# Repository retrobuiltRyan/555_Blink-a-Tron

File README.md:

# 555_Blink-a-Tron
Surface Mount device practice soldering activity.
Blink LEDS without logic using 555 timer + TLC5916 LED driver: 

Source reference TI white paper: https://www.ti.com/lit/an/slva346/slva346.pdf?ts=1731359344476&ref_url=https%253A%252F%252Fwww.google.com%252F

## Bill of Materials (BOM)

| Reference     | Value       | Footprint                                             | Qty | DigiKey P/N          |
|---------------|-------------|--------------------------------------------------------|-----|-----------------------|
| BT1           | Battery     | Battery:BatteryHolder_Keystone_1058_1x2032            | 1   | BU2032SM-GCT-ND       |
| C1, C2, C3    | 0.1uF       | Capacitor_SMD:C_1206_3216Metric                        | 3   | 1292-1605-1-ND        |
| C4            | 1uF         | Capacitor_SMD:C_1206_3216Metric                        | 1   | 1276-1068-1-ND        |
| D1–D8         | D           | Diode_SMD:D_1206_3216Metric                            | 8   | 67-1359-1-ND          |
| R1            | 37.4k       | Resistor_SMD:R_1206_3216Metric                         | 1   | 311-37.4KFRCT-ND      |
| R2            | 20k         | Resistor_SMD:R_1206_3216Metric                         | 1   | 311-20.0KFRCT-ND      |
| R3            | 3k – 6k     | Resistor_SMD:R_1206_3216Metric                         | 1   | 311-6.2KERCT-ND       |
| SW1           | SW_Push     | Button_Switch_SMD:SW_SPST_Omron_B3FS-100xP            | 1   | CKN12221-1-ND         |
| U1            | ICM7555xB   | Package_SO:SOIC-8_3.9x4.9mm_P1.27mm                    | 1   | 296-1336-1-ND         |
| U2            | TLC5916     | Package_SO:SOIC-16_3.9x9.9mm_P1.27mm                   | 1   | 296-22710-1-ND        |

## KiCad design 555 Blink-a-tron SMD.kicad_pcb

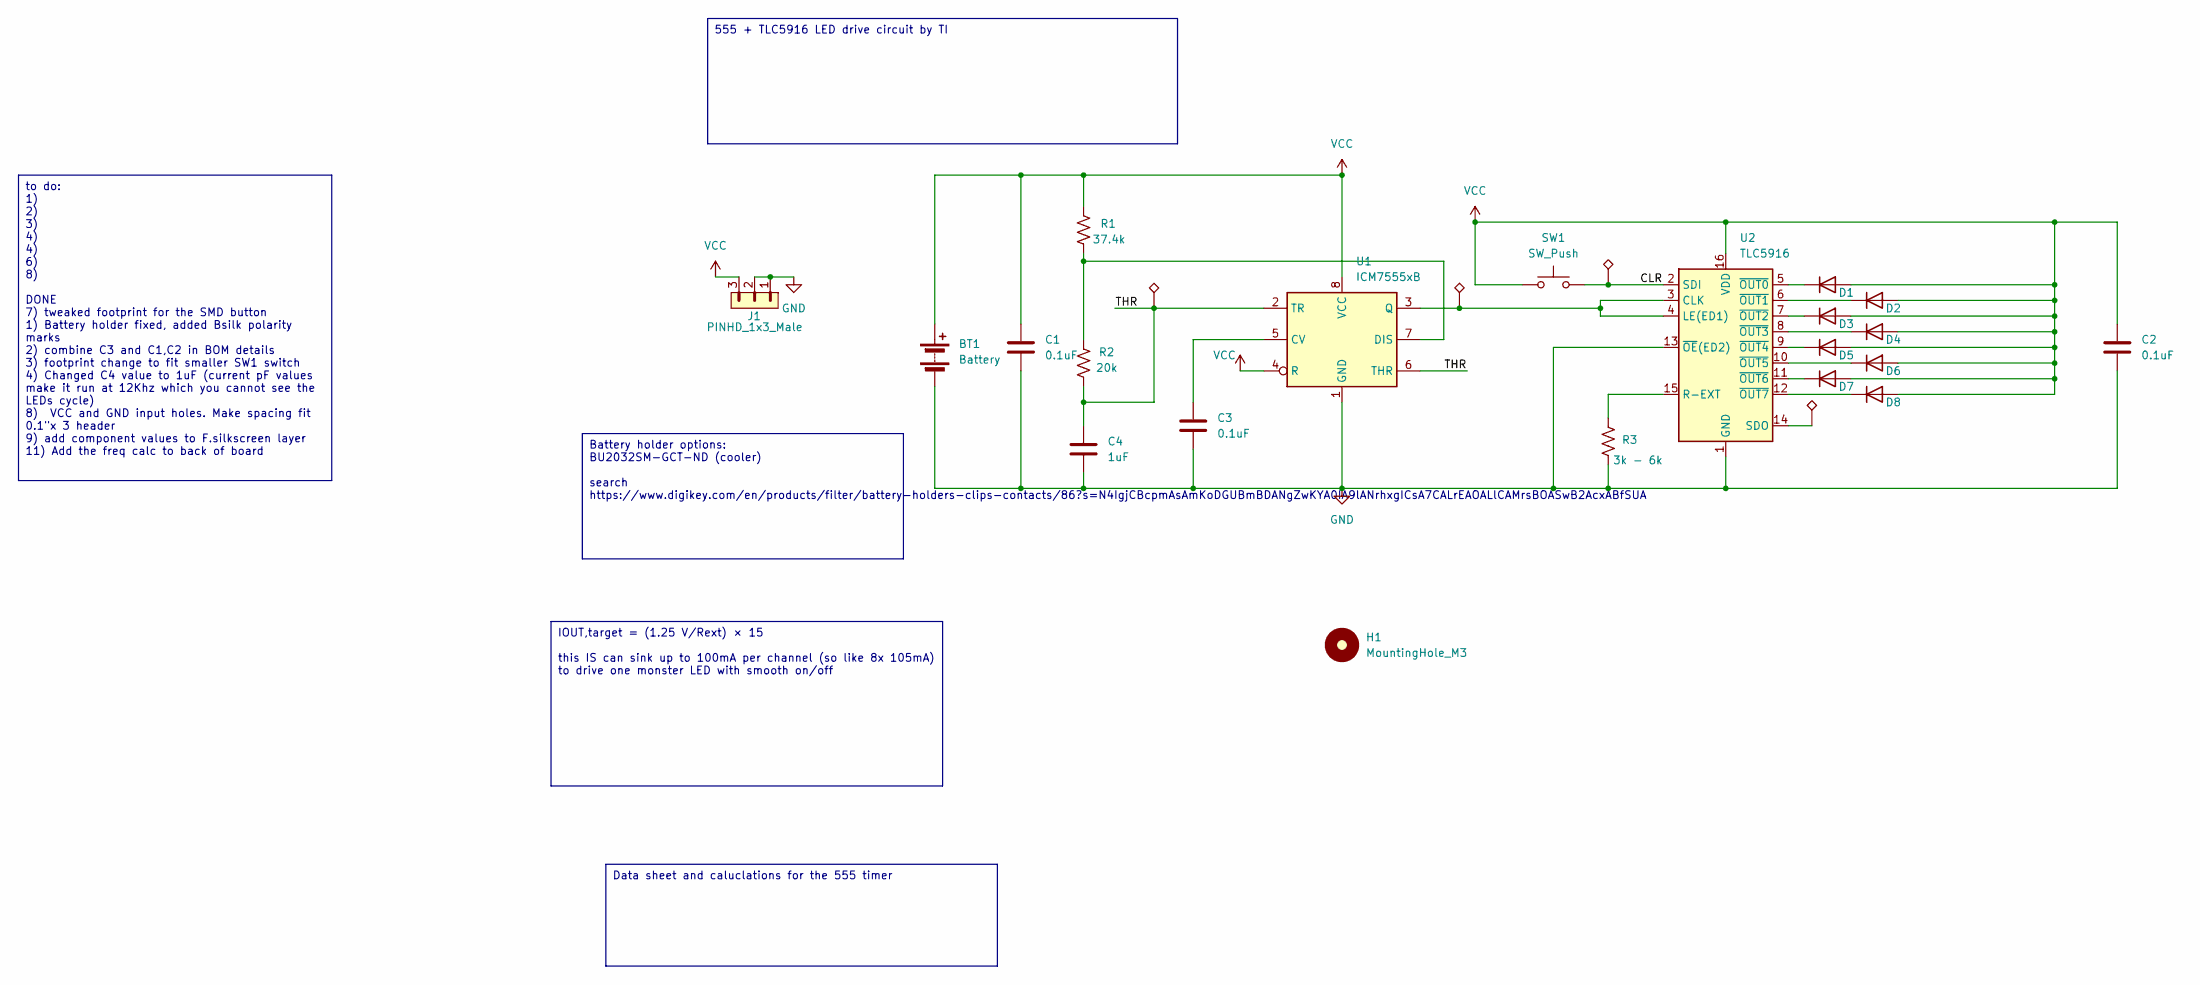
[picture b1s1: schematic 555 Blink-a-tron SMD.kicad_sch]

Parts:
BT1: Battery; BatteryHolder_Keystone_1058_1x2032; DigiKey P/N BU2032SM-GCT-ND
C1, C2, C3: 0.1uF; C_1206_3216Metric; DigiKey P/N 1292-1605-1-ND
C4: 1uF; C_1206_3216Metric; DigiKey P/N 1276-1068-1-ND
CLK1, CLK2: TestPoint_Alt; TestPoint_THTPad_1.5x1.5mm_Drill0.7mm
D1, D2, D3, D4, D5, D6, D7, D8: D; D_1206_3216Metric; DigiKey P/N 67-1359-1-ND
H1: MountingHole_M3; MountingHole_3.2mm_M3
J1: PINHD_1x3_Male; PinHeader_1x03_P2.54mm_Vertical
R1: 37.4k; R_1206_3216Metric; DigiKey P/N 311-37.4KFRCT-ND
R2: 20k; R_1206_3216Metric; DigiKey P/N 311-20.0KFRCT-ND
R3: 3k - 6k; R_1206_3216Metric; DigiKey P/N 311-6.2KERCT-ND
SDO1: TestPoint_Alt; TestPoint_THTPad_1.5x1.5mm_Drill0.7mm
SW1: SW_Push; SW_SPST_Omron_B3FS-100xP; DigiKey P/N CKN12221-1-ND
THR1: TestPoint_Alt; TestPoint_THTPad_1.5x1.5mm_Drill0.7mm
U1: ICM7555xB; SOIC-8_3.9x4.9mm_P1.27mm; DigiKey P/N 296-1336-1-ND
U2: TLC5916; SOIC-16_3.9x9.9mm_P1.27mm; DigiKey P/N 296-22710-1-ND

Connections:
/CLR: CLK2.1, SW1.2, U2.2 (SDI); also elsewhere on the board
/THR: C4.1, R2.1, THR1.1, U1.2 (TR), U1.6 (THR)
GND: BT1.2 (-), C1.2, C2.2, C3.2, C4.2, J1.1, J1.2, R3.1, U1.1 (GND), U2.1 (GND), U2.13 (~OE(ED2))
unnamed: D1.1 (K), U2.5 (~OUT0)
unnamed: D2.1 (K), U2.6 (~OUT1)
unnamed: D3.1 (K), U2.7 (~OUT2)
unnamed: D4.1 (K), U2.8 (~OUT3)
unnamed: D5.1 (K), U2.9 (~OUT4)
unnamed: D6.1 (K), U2.10 (~OUT5)
unnamed: D7.1 (K), U2.11 (~OUT6)
unnamed: D8.1 (K), U2.12 (~OUT7)
unnamed: C3.1, U1.5 (CV)
unnamed: R1.1, R2.2, U1.7 (DIS)
unnamed: CLK1.1, U1.3 (Q), U2.3 (CLK), U2.4 (LE(ED1))
unnamed: R3.2, U2.15 (R-EXT)
unnamed: SDO1.1, U2.14 (SDO)
VCC: BT1.1 (+), C1.1, C2.1, D1.2 (A), D2.2 (A), D3.2 (A), D4.2 (A), D5.2 (A), D6.2 (A), D7.2 (A), D8.2 (A), J1.3, R1.2, SW1.1, U1.4 (R), U1.8 (VCC), U2.16 (VDD)

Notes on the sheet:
Battery holder options: BU2032SM-GCT-ND (cooler) search https://www.digikey.com/en/products/filter/battery-holders-clips-contacts/86?s=N4IgjCBcpmAsAmKoDGUBmBDANgZwKYA0IA9lANrhxgICsA7CALrEAOALlCAMrsBOASwB2AcxABfSUA
555 + TLC5916 LED drive circuit by TI
Data sheet and caluclations for the 555 timer
IOUT,target = (1.25 V/Rext) × 15 this IS can sink up to 100mA per channel (so like 8x 105mA) to drive one monster LED with smooth on/off
to do: 1) 2) 3) 4) 4) 6) 8) DONE 7) tweaked footprint for the SMD button 1) Battery holder fixed, added Bsilk polarity marks 2) combine C3 and C1,C2 in BOM details 3) footprint change to fit smaller SW1 switch 4) Changed C4 value to 1uF (current pF values make it run at 12Khz which you cannot see t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

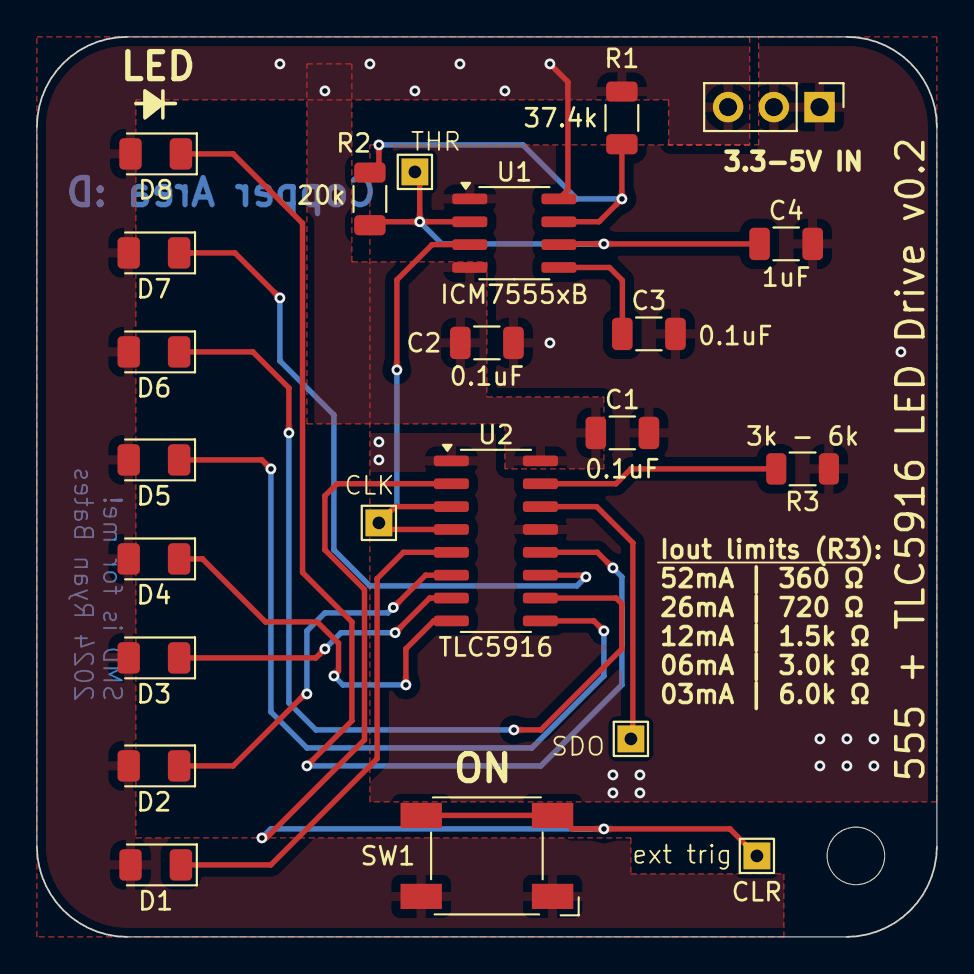
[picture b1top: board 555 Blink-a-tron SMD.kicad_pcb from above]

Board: 2 copper layers, 50.0 x 50.0 mm, 25 parts (1 on the bottom side), 17 nets.

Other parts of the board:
CLR: TestPoint_Alt; TestPoint_THTPad_1.5x1.5mm_Drill0.7mm

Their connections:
/CLR: CLR.1; also elsewhere on the board

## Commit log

2025-07-30 PCB design files (kiCAD)
2025-07-30 Gerbers
    JLCPCB
